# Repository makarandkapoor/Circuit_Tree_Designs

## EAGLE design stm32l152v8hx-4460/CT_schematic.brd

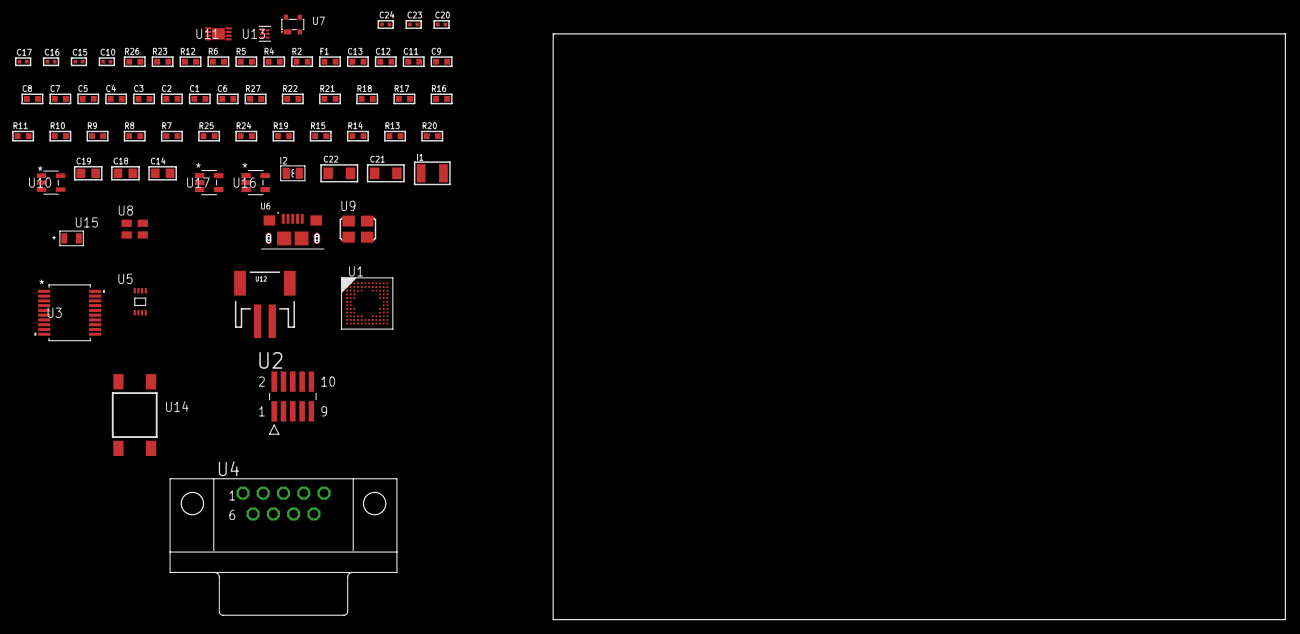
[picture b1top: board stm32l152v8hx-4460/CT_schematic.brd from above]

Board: 2 copper layers, 69 parts (0 on the bottom side), 49 nets, no tracks yet.

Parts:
C1, C2, C3, C4, C5, C7: 1e-07; C0603
C6: 4.7e-06; C0603
C8: 1e-08; C0603
C9, C11, C12, C13: 1e-06; C0603
C10, C20: 1e-07; C0402
C14: 4.7e-06; C0805
C15, C16, C17, C23, C24: 1e-08; C0402
C18, C19: 1e-05; C0805
C21, C22: 1e-05; C1206
F1: 240.0; L0603
I1: 1.5e-05; L1210
I2: 3.3e-06; L0806
R2: 1000.0; R0603
R4: 4700.0; R0603
R5, R6: 2200.0; R0603
R7, R8, R9, R10, R11, R16, R17, R18, R21, R22, R27: 10000.0; R0603
R12: 5.0; R0603
R13, R14, R15: 100000.0; R0603
R19: 220000.0; R0603
R20: 1000000.0; R0603
R23: 9100.0; R0603
R24: 680000.0; R0603
R25: 120000.0; R0603
R26: 2000.0; R0603
U1: STM32L152V8H6; UFBGA100
U2: FTSH-105-01-L-DV-K; SAMTEC_FTSH-105-01-L-DV-K
U3: MAX3218EAP+T; SSOP-20
U4: 182-009-113R531; 182-009-MALE
U5: 24AA128T-I/MNY; TDFN-8/6MM
U6: 10118193-0001LF; FCI_10118193-0001LF
U7: prtr5v0u2ax; SOT143B
U8: ASEK-32.768KHz-ECST; ASEK
U9: ASFL1-25MHZ-NCS; ASFL1
U10: ltc3406es5; TSOT-23-5
U11: MCP73831T-2ACI/MC; DFN8_2X3MC
U12: S2B-PH-SM4-TB(LF)(SN); JST-2-SMD
U13: TPS3895ADRYR; SON-6
U14: 4-1437565-2; SW_4-1437565-2
U15: Q65110A2395; LGM67K-G1J2-24-Z
U16, U17: nc7sz125m5x; NC7SZ125M5X

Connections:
CLK_U1_D1: U1.D1, U8.3
CLK_U1_F1: U1.F1, U9.3
GND: C1.2, C2.2, C3.2, C4.2, C5.2, C6.2, C7.2, C8.2, C9.2, C10.2, C11.2, C12.2, C13.2, C15.2, C16.2, C17.2, C18.2, C19.1, C19.2, C20.2, C21.2, C22.2, C23.2, C24.2, R2.2, R7.2, R11.2, R12.2, R16.2, R18.2, R19.2, R23.2, R25.2, R26.2, U1.D3, U1.E3, U1.F2, U1.F11, U1.F12, U1.J1, U1.K1, U2.3, U2.5, U3.5, U3.17, U3.20, U4.5, U5.4, U5.7, U6.5, U6.6, U6.7, U6.8, U6.9, U7.1, U8.2, U9.2, U10.2, U11.6, U11.9, U12.2, U13.2, U15.C, U16.2, U16.3, U17.1, U17.3
INPUT_USBPOWER_5V: C21.1, R27.2, U6.1, U7.4, U11.1, U11.2
NET_U1_A3: R5.1, U1.A3, U5.6
NET_U1_A4: R7.1, U1.A4
NET_U1_B3: R6.1, U1.B3, U5.5
NET_U1_E2: C7.1, U1.E2
NET_U1_H2: R4.1, U1.H2, U17.4
NET_U1_M1: C8.1, C9.1, F1.1, U1.L1, U1.M1
NET_U1_M12: U14.3, U14.4
NET_U2_9: R12.1, U2.9
NET_U3_1: I1.1, U3.1
NET_U3_2: R13.1, U3.2
NET_U3_3: R14.1, U3.3
NET_U3_4: R15.1, U3.4
NET_U3_15: C13.1, U3.15
NET_U3_16: C14.2, U3.16
NET_U3_18: C14.1, U3.18
NET_U3_19: C12.1, U3.19
NET_U4_2: U3.12, U4.2
NET_U4_3: U3.14, U4.3
NET_U4_7: U3.11, U4.7
NET_U4_8: U3.13, U4.8
NET_U5_1: R16.1, U5.1
NET_U5_2: R17.1, U5.2
NET_U5_3: R18.1, U5.3
NET_U10_3: I2.1, U10.3
NET_U10_5: R19.1, R20.1, U10.5
NET_U10_ATNET_3: I2.2, R20.2
NET_U11_5: R27.1, U11.5
NET_U11_8: R26.1, U11.8
NET_U13_1: R22.1, R23.1, U13.1
NET_U13_3: R24.2, R25.1, U13.3
NET_U13_4: R21.1, U13.4, U16.4, U17.2
NET_U14_1: R2.1, U14.1, U14.2
PROC_SYS_JTCK_SWCLK: R11.1, U1.A10, U2.4
PROC_SYS_JTDI: R9.1, U1.A9, U2.8
PROC_SYS_JTDO_TRACESWO: U1.A8, U2.6
PROC_SYS_JTMS_SWDIO: R10.1, U1.A11, U2.2
PROC_USART2_CTS: U1.B8, U3.8
PROC_USART2_RTS: U1.B7, U3.10
PROC_USART2_RX: U1.B6, U3.9
PROC_USART2_TX: U1.A6, U3.7
PROC_USB_DM: U1.B12, U6.2, U7.3
PROC_USB_DP: U1.A12, U6.3, U7.2
RST_OUT_U2_JTAG_RST_B: R8.1, U2.10, U16.1
VCC_S1_3V7: C18.1, C22.1, U10.4, U11.3, U11.4, U12.1
VCC_TIER1_3V3: C1.1, C2.1, C3.1, C4.1, C5.1, C6.1, C10.1, C11.1, C15.1, C16.1, C17.1, C19.2, C20.1, C23.1, C24.1, F1.2, I1.2, I2.2, R4.2, R5.2, R6.2, R8.2, R9.2, R10.2, R13.2, R14.2, R15.2, R17.2, R20.2, R21.2, R22.2, R24.1, U1.C4, U1.G2, U1.G11, U1.G12, U1.H3, U2.1, U3.6, U5.8, U8.4, U9.4, U13.6, U16.5, U17.5

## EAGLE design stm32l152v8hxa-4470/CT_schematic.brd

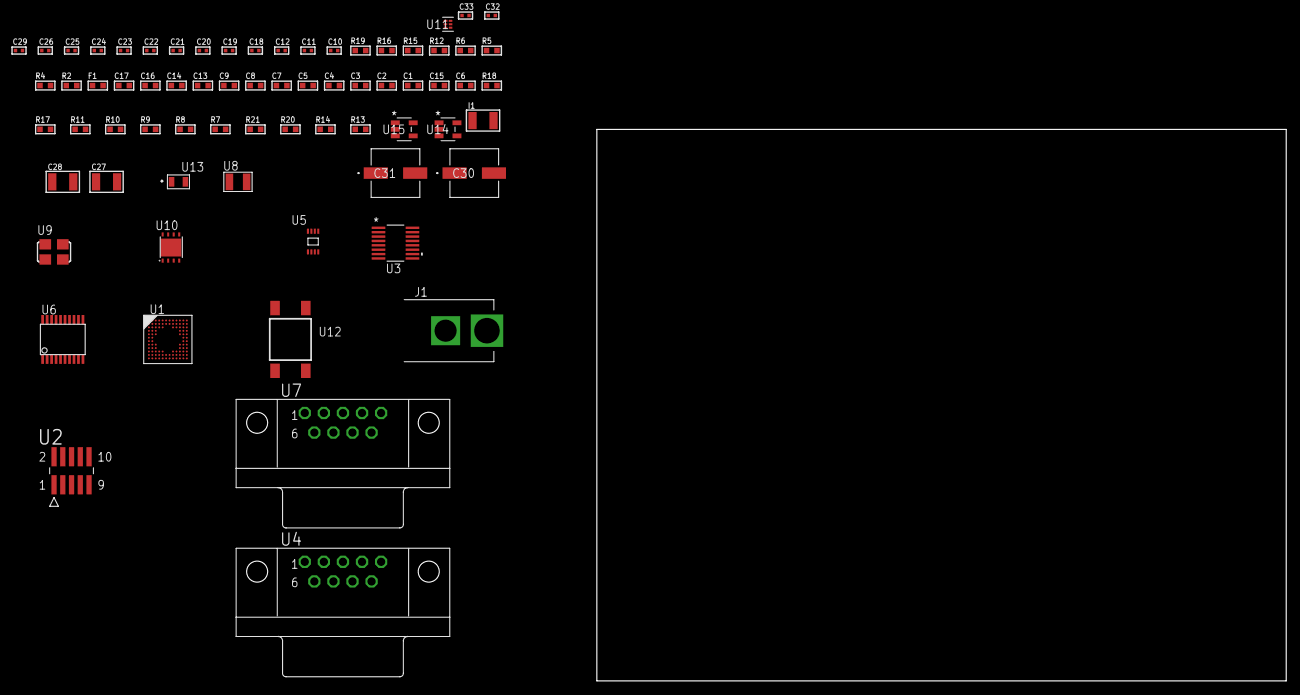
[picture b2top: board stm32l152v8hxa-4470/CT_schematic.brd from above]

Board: 2 copper layers, 100.0 x 80.0 mm, 70 parts (0 on the bottom side), 53 nets, no tracks yet.

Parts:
C1, C2, C3, C4, C5, C7: 1e-07; C0603
C6: 4.7e-06; C0603
C8: 1e-08; C0603
C9, C13, C14, C16, C17: 1e-06; C0603
C10, C11: 1e-11; C0402
C12, C19, C20, C21, C22, C23, C24, C29: 1e-07; C0402
C15: 2.2e-07; C0603
C18, C25, C26, C32, C33: 1e-08; C0402
C27, C28: 1e-05; C1210
C30, C31: 0.0001; EXV-9H
F1: 240.0; L0603
I1: 1e-05; L1210
J1: PJ-037B; PJ-037B_PACKAGE
R2, R16: 1000.0; R0603
R4: 4700.0; R0603
R5, R6: 2200.0; R0603
R7, R8, R9, R10, R11, R17, R18: 10000.0; R0603
R12: 5.0; R0603
R13, R14: 100000.0; R0603
R15: 2231.0; R0603
R19: 9100.0; R0603
R20: 680000.0; R0603
R21: 120000.0; R0603
U1: STM32L152V8H6A; UFBGA100
U2: FTSH-105-01-L-DV-K; SAMTEC_FTSH-105-01-L-DV-K
U3: LTC2804CGN-1#PBF; SSOP-16
U4, U7: 182-009-113R531; 182-009-MALE
U5: 24AA16-I/MC; TDFN-8/6MM
U6: SP3203ECY-L/TR; TSSOP20-I
U8: ABS07-32.768KHZ-7-T
U9: ASFL1-25MHZ-NCS; ASFL1
U10: LP3878SDX-ADJ/NOPB; WSON-8
U11: TPS3895ADRYR; SON-6
U12: 4-1437565-2; SW_4-1437565-2
U13: Q65110A2395; LGM67K-G1J2-24-Z
U14, U15: nc7sz125m5x; NC7SZ125M5X

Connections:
CLK_CRYSTAL_U1_D1: C10.1, U1.D1, U8.1
CLK_CRYSTAL_U1_E1: C11.1, U1.E1, U8.2
CLK_U1_F1: U1.F1, U9.3
GND: C1.2, C2.2, C3.2, C4.2, C5.2, C6.2, C7.2, C8.2, C9.2, C10.2, C11.2, C12.2, C13.2, C14.2, C16.2, C17.2, C18.2, C19.2, C20.2, C23.2, C24.2, C25.2, C26.2, C27.2, C28.2, C29.2, C30.2, C31.2, C32.2, C33.2, J1.2, R2.2, R7.2, R11.2, R12.2, R16.2, R19.2, R21.2, U1.D3, U1.E3, U1.F2, U1.F11, U1.F12, U1.J1, U1.K1, U2.3, U2.5, U3.8, U4.5, U5.4, U5.7, U6.18, U7.5, U9.2, U10.3, U10.PAD, U11.2, U13.C, U14.2, U14.3, U15.1, U15.3
NET_U1_A3: R5.1, U1.A3, U5.6
NET_U1_A4: R7.1, U1.A4
NET_U1_B3: R6.1, U1.B3, U5.5
NET_U1_E2: C7.1, U1.E2
NET_U1_H2: R4.1, U1.H2, U15.4
NET_U1_M1: C8.1, C9.1, F1.1, U1.L1, U1.M1
NET_U1_M12: U12.3, U12.4
NET_U2_9: R12.1, U2.9
NET_U3_6: C13.1, U3.6
NET_U3_7: C15.1, I1.2, U3.7
NET_U3_9: C14.1, U3.9
NET_U3_10: C15.2, U3.10
NET_U3_11: R13.1, U3.11
NET_U4_2: U3.1, U4.2
NET_U4_3: U3.3, U4.3
NET_U4_7: U3.2, U4.7
NET_U4_8: U3.4, U4.8
NET_U6_1: C21.1, U6.1
NET_U6_2: C23.1, U6.2
NET_U6_3: C21.2, U6.3
NET_U6_4: C22.1, U6.4
NET_U6_5: C22.2, U6.5
NET_U6_6: C24.1, U6.6
NET_U7_2: U6.14, U7.2
NET_U7_3: U6.17, U7.3
NET_U7_7: U6.13, U7.7
NET_U7_8: U6.16, U7.8
NET_U10_1: C26.1, U10.1
NET_U10_6: R15.2, R16.1, U10.6
NET_U10_8: R14.1, U10.8
NET_U11_1: R18.1, R19.1, U11.1
NET_U11_3: R20.2, R21.1, U11.3
NET_U11_4: R17.1, U11.4, U14.4, U15.2
NET_U12_1: R2.1, U12.1, U12.2
PROC_SYS_JTCK_SWCLK: R11.1, U1.A10, U2.4
PROC_SYS_JTDI: R9.1, U1.A9, U2.8
PROC_SYS_JTDO_TRACESWO: U1.A8, U2.6
PROC_SYS_JTMS_SWDIO: R10.1, U1.A11, U2.2
PROC_USART1_CTS: U1.B12, U6.8
PROC_USART1_RTS: U1.A12, U6.10
PROC_USART1_RX: U1.B4, U6.11
PROC_USART1_TX: U1.B5, U6.7
PROC_USART2_CTS: U1.B8, U3.13
PROC_USART2_RTS: U1.B7, U3.15
PROC_USART2_RX: U1.B6, U3.16
PROC_USART2_TX: U1.A6, U3.14
RST_OUT_U2_JTAG_RST_B: R8.1, U2.10, U14.1
VCC_S1_14V2: C27.1, C30.1, C31.1, J1.1, R14.2, U10.4
VCC_TIER1_3V3: C1.1, C2.1, C3.1, C4.1, C5.1, C6.1, C12.1, C16.1, C17.1, C18.1, C19.1, C20.1, C25.1, C28.1, C29.1, C32.1, C33.1, F1.2, I1.1, R4.2, R5.2, R6.2, R8.2, R9.2, R10.2, R13.2, R15.1, R17.2, R18.2, R20.1, U1.C4, U1.G2, U1.G11, U1.G12, U1.H3, U2.1, U3.5, U3.12, U5.8, U6.12, U6.19, U9.4, U10.5, U11.6, U14.5, U15.5

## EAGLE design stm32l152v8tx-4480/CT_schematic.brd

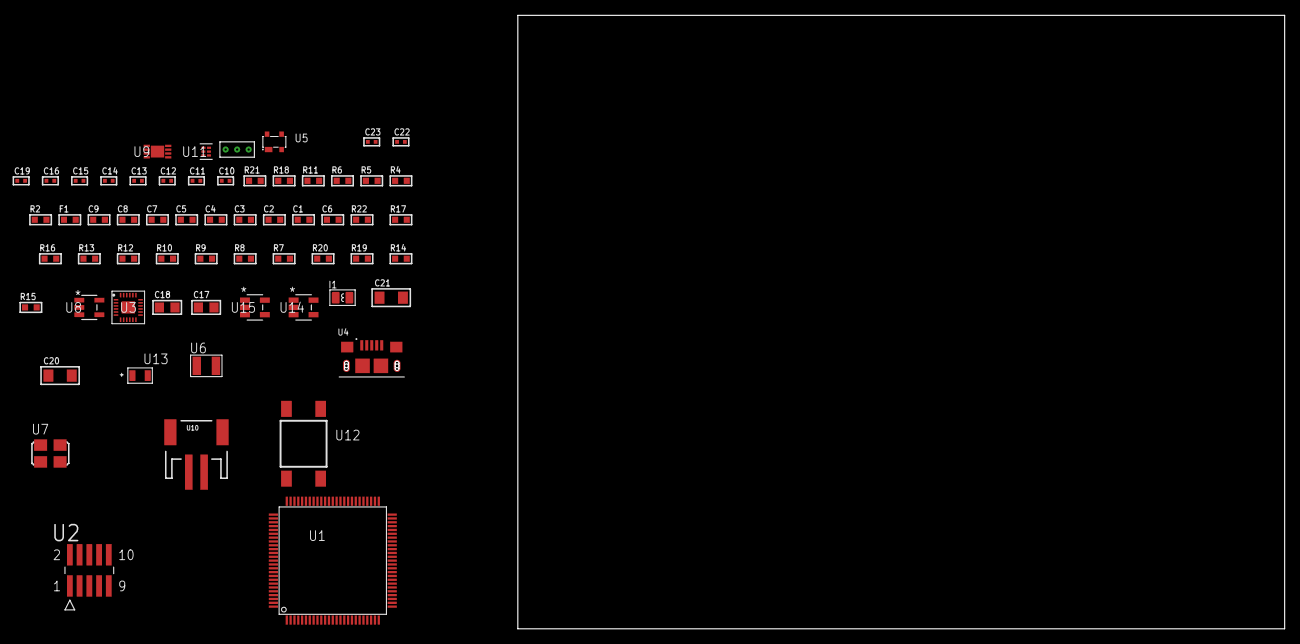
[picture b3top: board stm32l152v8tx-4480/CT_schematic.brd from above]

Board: 2 copper layers, 122.6 x 80.0 mm, 61 parts (0 on the bottom side), 37 nets, no tracks yet.

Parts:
C1, C2, C3, C4, C5, C7: 1e-07; C0603
C6: 4.7e-06; C0603
C8: 1e-08; C0603
C9: 1e-06; C0603
C10, C11: 1e-11; C0402
C12, C13, C14, C19: 1e-07; C0402
C15, C16, C22, C23: 1e-08; C0402
C17, C18: 1e-05; C0805
C20, C21: 1e-05; C1206
F1: 240.0; L0603
I1: 3.3e-06; L0806
R2: 1000.0; R0603
R4: 4700.0; R0603
R5, R6: 2200.0; R0603
R7, R8, R9, R10, R12, R13, R16, R17, R22: 10000.0; R0603
R11: 5.0; R0603
R14: 220000.0; R0603
R15: 1000000.0; R0603
R18: 9100.0; R0603
R19: 680000.0; R0603
R20: 120000.0; R0603
R21: 2000.0; R0603
U1: STM32L152V8T6; LQFP100
U2: FTSH-105-01-L-DV-K; SAMTEC_FTSH-105-01-L-DV-K
U3: MPU-9250; QFN24_2
U4: 10118193-0001LF; FCI_10118193-0001LF
U5: prtr5v0u2ax; SOT143B
U6: ABS07-32.768KHZ-7-T
U7: ASFL1-25MHZ-NCS; ASFL1
U8: ltc3406es5; TSOT-23-5
U9: MCP73831T-2ACI/MC; DFN8_2X3MC
U10: S2B-PH-SM4-TB(LF)(SN); JST-2-SMD
U11: TPS3895ADRYR; SON-6
U12: 4-1437565-2; SW_4-1437565-2
U13: Q65110A2395; LGM67K-G1J2-24-Z
U14, U15: nc7sz125m5x; NC7SZ125M5X
U16: Dummy; DUMMY_PACKAGE_138

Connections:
CLK_CRYSTAL_U1_8: C10.1, U1.8, U6.1
CLK_CRYSTAL_U1_9: C11.1, U1.9, U6.2
CLK_U1_12: U1.12, U7.3
GND: C1.2, C2.2, C3.2, C4.2, C5.2, C6.2, C7.2, C8.2, C9.2, C10.2, C11.2, C12.2, C13.2, C14.2, C15.2, C16.2, C17.2, C18.1, C18.2, C19.2, C20.2, C21.2, C22.2, C23.2, R2.2, R7.2, R11.2, R14.2, R18.2, R20.2, R21.2, U1.10, U1.19, U1.20, U1.27, U1.49, U1.74, U1.99, U2.3, U2.5, U3.18, U3.20, U3.25, U4.5, U4.6, U4.7, U4.8, U4.9, U5.1, U7.2, U8.2, U9.6, U9.9, U10.2, U11.2, U13.C, U14.2, U14.3, U15.1, U15.3, U16.1
INPUT_USBPOWER_5V: C20.1, R22.2, U4.1, U5.4, U9.1, U9.2
NET_U1_6: C7.1, U1.6
NET_U1_14: R4.1, U1.14, U15.4
NET_U1_22: C8.1, C9.1, F1.1, U1.21, U1.22
NET_U1_92: R5.1, U1.92, U3.23
NET_U1_93: R6.1, U1.93, U3.24
NET_U1_94: R7.1, U1.94
NET_U1_98: U12.3, U12.4
NET_U2_9: R11.1, U2.9
NET_U3_9: R13.1, U3.9
NET_U3_10: C13.1, U3.10
NET_U3_22: R12.1, U3.22
NET_U8_3: I1.1, U8.3
NET_U8_5: R14.1, R15.1, U8.5
NET_U8_ATNET_3: I1.2, R15.2
NET_U9_5: R22.1, U9.5
NET_U9_8: R21.1, U9.8
NET_U11_1: R17.1, R18.1, U11.1
NET_U11_3: R19.2, R20.1, U11.3
NET_U11_4: R16.1, U11.4, U14.4, U15.2
NET_U12_1: R2.1, U12.1, U12.2
PROC_GPIO_TO_U3_FSYNC: U1.2, U3.11
PROC_GPIO_TO_U3_INT_B: U1.1, U3.12
PROC_PE4: U1.3, U16.2
PROC_PE5: U1.4, U16.3
PROC_SYS_JTCK_SWCLK: R9.1, U1.76, U2.4
PROC_SYS_JTDO_TRACESWO: U1.89, U2.6
PROC_SYS_JTMS_SWDIO: R10.1, U1.72, U2.2
PROC_USB_DM: U4.2, U5.3
PROC_USB_DP: U4.3, U5.2
RST_OUT_U2_JTAG_RST_B: R8.1, U2.10, U14.1
VCC_S1_3V7: C17.1, C21.1, U8.4, U9.3, U9.4, U10.1
VCC_TIER1_3V3: C1.1, C2.1, C3.1, C4.1, C5.1, C6.1, C12.1, C14.1, C15.1, C16.1, C18.2, C19.1, C22.1, C23.1, F1.2, I1.2, R4.2, R5.2, R6.2, R8.2, R9.2, R10.2, R12.2, R13.2, R15.2, R16.2, R17.2, R19.1, U1.11, U1.28, U1.50, U1.75, U1.100, U2.1, U3.1, U3.8, U3.13, U7.4, U11.6, U14.5, U15.5

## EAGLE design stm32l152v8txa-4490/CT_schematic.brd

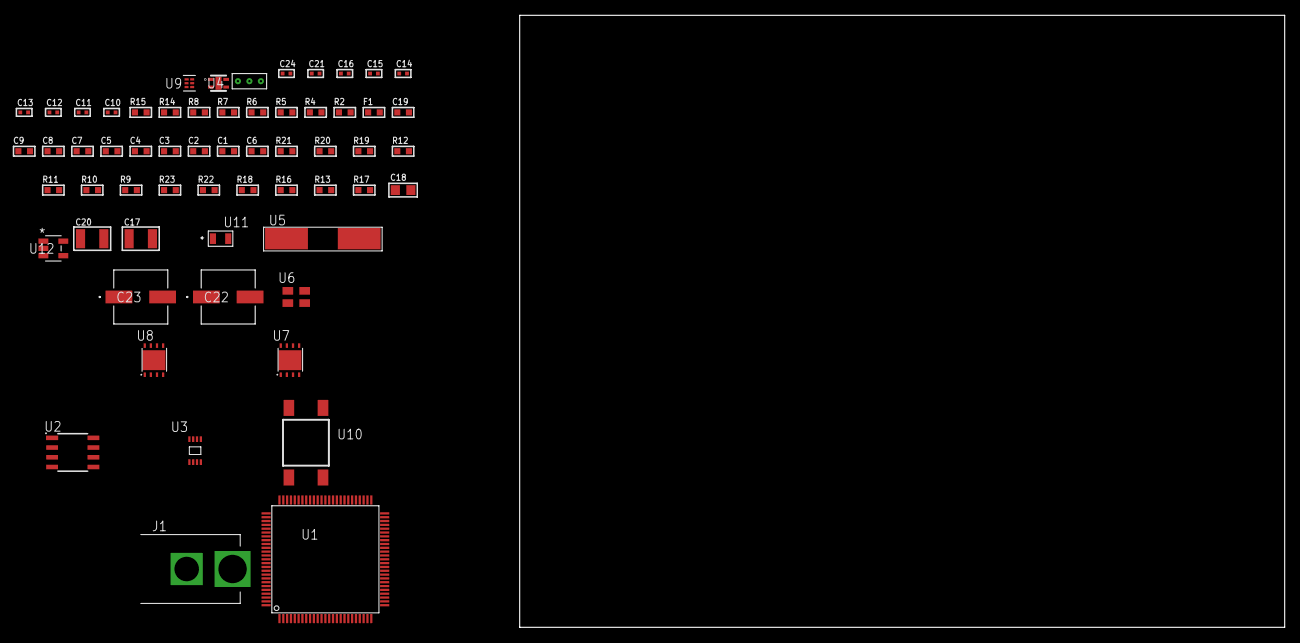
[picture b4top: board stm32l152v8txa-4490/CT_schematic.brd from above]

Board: 2 copper layers, 100.0 x 80.0 mm, 60 parts (0 on the bottom side), 33 nets, no tracks yet.

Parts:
C1, C2, C3, C4, C5, C7: 1e-07; C0603
C6: 4.7e-06; C0603
C8: 1e-08; C0603
C9: 1e-06; C0603
C10, C11: 1e-11; C0402
C12, C13, C15, C16, C24: 1e-08; C0402
C14, C21: 1e-07; C0402
C17, C20: 1e-05; C1210
C18: 1e-05; C0805
C19: 8e-07; R0603
C22, C23: 0.0001; EXV-9H
F1: 240.0; L0603
J1: PJ-037B; PJ-037B_PACKAGE
R2, R15: 1000.0; R0603
R4: 4700.0; R0603
R5, R6, R7, R8: 2200.0; R0603
R9, R10, R11, R12, R19, R20: 10000.0; R0603
R13, R16, R18: 100000.0; R0603
R14: 806.0; R0603
R17: 153694.38; R0603
R21: 82000.0; R0603
R22: 300000.0; R0603
R23: 120000.0; R0603
U1: STM32L152V8T6A; LQFP100
U2: AT25M02-SSHD-T; SOIC-8
U3: 24AA01T-I/MNY; TDFN-8/6MM
U4: Si7034-A10-IM; SI7034-A10-IM
U5: ABLS-25.000MHZ-B2F-T
U6: ASEK-32.768KHz-ECST; ASEK
U7: LP3878SDX-ADJ/NOPB; WSON-8
U8: LP2951ACSDX/NOPB; WSON-8
U9: TPS3895ADRYR; SON-6
U10: 4-1437565-2; SW_4-1437565-2
U11: Q65110A2395; LGM67K-G1J2-24-Z
U12: nc7sz125m5x; NC7SZ125M5X
U13: Dummy; DUMMY_PACKAGE_133

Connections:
CLK_CRYSTAL_U1_12: C10.1, U1.12, U5.1
CLK_CRYSTAL_U1_13: C11.1, U1.13, U5.2
CLK_U1_8: U1.8, U6.3
GND: C1.2, C2.2, C3.2, C4.2, C5.2, C6.2, C7.2, C8.2, C9.2, C10.2, C11.2, C12.2, C13.2, C14.2, C15.2, C16.2, C17.2, C18.2, C19.2, C20.2, C21.2, C22.2, C23.2, C24.2, J1.2, R2.2, R9.2, R15.2, R18.2, R21.2, R23.2, U1.10, U1.19, U1.20, U1.27, U1.49, U1.74, U1.99, U2.4, U3.4, U4.5, U6.2, U7.3, U7.PAD, U8.3, U8.4, U8.PAD, U9.2, U11.C, U12.1, U12.3, U13.1
NET_U1_6: C7.1, U1.6
NET_U1_14: R4.1, U1.14, U12.4
NET_U1_22: C8.1, C9.1, F1.1, U1.21, U1.22
NET_U1_47: R7.1, U1.47, U3.6
NET_U1_48: R8.1, U1.48, U3.5
NET_U1_92: R5.1, U1.92, U4.2
NET_U1_93: R6.1, U1.93, U4.4
NET_U1_94: R9.1, U1.94
NET_U1_98: U10.3, U10.4
NET_U2_3: R10.1, U2.3
NET_U2_7: R12.1, U2.7
NET_U7_1: C16.1, U7.1
NET_U7_6: R14.2, R15.1, U7.6
NET_U7_8: R13.1, U7.8
NET_U8_5: R16.1, U8.5
NET_U8_7: R17.2, R18.1, U8.7
NET_U9_1: R20.1, R21.1, U9.1
NET_U9_3: R22.2, R23.1, U9.3
NET_U9_4: R19.1, U9.4, U12.2
NET_U10_1: R2.1, U10.1, U10.2
PROC_ADC_IN20: U1.53, U13.2
PROC_ADC_IN22: U1.38, U13.3
PROC_SPI1_MISO: U1.31, U2.2
PROC_SPI1_MOSI: U1.32, U2.5
PROC_SPI1_NSS: R11.1, U1.29, U2.1
PROC_SPI1_SCK: U1.30, U2.6
VCC_S1_13V6: C17.1, C19.1, C22.1, C23.1, J1.1, R13.2, U7.4, U8.8
VCC_TIER1_1V8: C1.1, C2.1, C3.1, C4.1, C5.1, C6.1, C12.1, C13.1, C14.1, C18.1, C21.1, C24.1, F1.2, R4.2, R5.2, R6.2, R7.2, R8.2, R10.2, R11.2, R12.2, R14.1, R19.2, R20.2, R22.1, U1.11, U1.28, U1.50, U1.75, U1.100, U2.8, U3.7, U3.8, U4.1, U7.5, U9.6, U12.5
VCC_TIER1_3V3: C15.1, C20.1, R16.2, R17.1, U6.4, U8.1

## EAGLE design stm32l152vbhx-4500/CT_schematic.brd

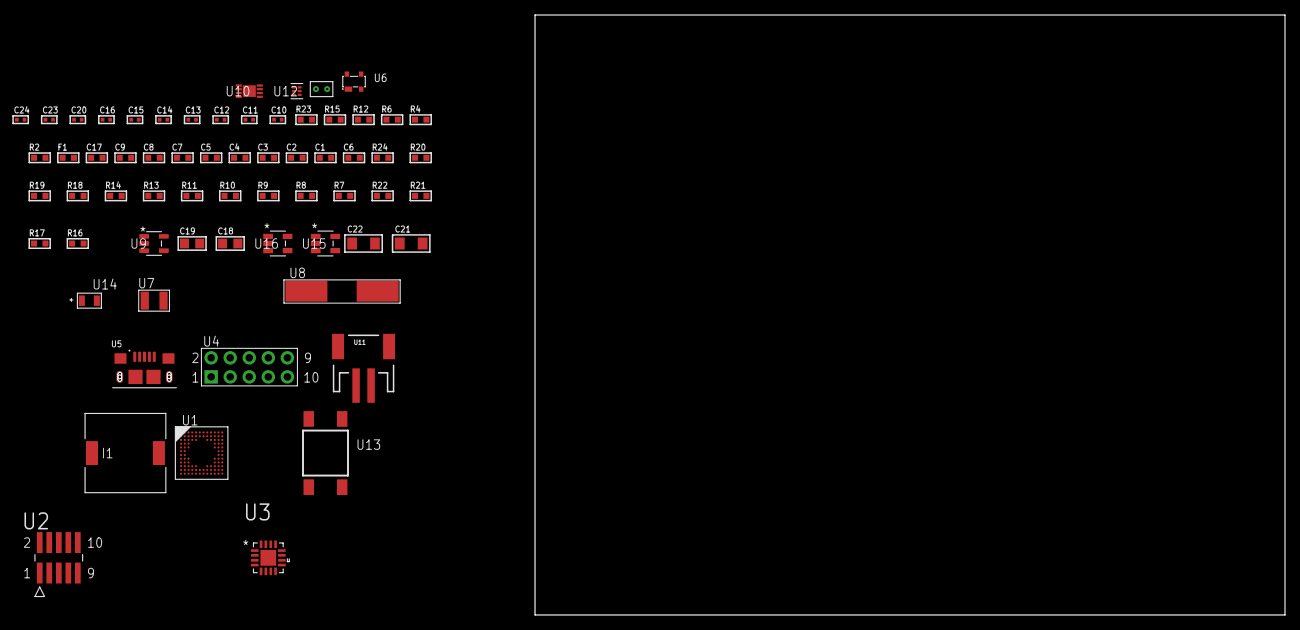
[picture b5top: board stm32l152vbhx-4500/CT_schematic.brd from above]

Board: 2 copper layers, 64 parts (0 on the bottom side), 40 nets, no tracks yet.

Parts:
C1, C2, C3, C4, C5, C7: 1e-07; C0603
C6: 4.7e-06; C0603
C8: 1e-08; C0603
C9, C17: 1e-06; C0603
C10, C11, C12, C13: 1e-11; C0402
C14, C15, C16, C20: 1e-07; C0402
C18, C19: 1e-05; C0805
C21, C22: 1e-05; C1206
C23, C24: 1e-08; C0402
F1: 240.0; L0603
I1: 5.2e-06; DR1040
R2: 1000.0; R0603
R4: 4700.0; R0603
R6: 2200.0; R0603
R7, R8, R9, R10, R11, R13, R14, R18, R19, R24: 10000.0; R0603
R12: 5.0; R0603
R15: 47.0; R0603
R16: 309473.68421053; R0603
R17: 1000000.0; R0603
R20: 18000.0; R0603
R21: 470000.0; R0603
R22: 120000.0; R0603
R23: 2000.0; R0603
U1: STM32L152VBH6; UFBGA100
U2: FTSH-105-01-L-DV-K; SAMTEC_FTSH-105-01-L-DV-K
U3: TSC2013QRSARQ1; QFN65P400X400X100-17N
U4: HTSS-105-01-G-D
U5: 10118193-0001LF; FCI_10118193-0001LF
U6: prtr5v0u2ax; SOT143B
U7: ABS07-32.768KHZ-7-T
U8: ABLS-25.000MHZ-B2F-T
U9: ltc3406es5; TSOT-23-5
U10: MCP73831T-2ACI/MC; DFN8_2X3MC
U11: S2B-PH-SM4-TB(LF)(SN); JST-2-SMD
U12: TPS3895ADRYR; SON-6
U13: 4-1437565-2; SW_4-1437565-2
U14: Q65110A2395; LGM67K-G1J2-24-Z
U15, U16: nc7sz125m5x; NC7SZ125M5X
U17: Dummy; DUMMY_PACKAGE_135

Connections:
CLK_CRYSTAL_U1_D1: C10.1, U1.D1, U7.1
CLK_CRYSTAL_U1_E1: C11.1, U1.E1, U7.2
CLK_CRYSTAL_U1_F1: C12.1, U1.F1, U8.1
CLK_CRYSTAL_U1_G1: C13.1, U1.G1, U8.2
GND: C1.2, C2.2, C3.2, C4.2, C5.2, C6.2, C7.2, C8.2, C9.2, C10.2, C11.2, C12.2, C13.2, C14.2, C18.2, C19.1, C19.2, C20.2, C21.2, C22.2, C23.2, C24.2, R2.2, R7.2, R11.2, R12.2, R16.2, R20.2, R22.2, R23.2, U1.D3, U1.E3, U1.F2, U1.F11, U1.F12, U1.J1, U1.K1, U2.3, U2.5, U3.17, U4.9, U5.5, U5.6, U5.7, U5.8, U5.9, U6.1, U9.2, U10.6, U10.9, U11.2, U12.2, U14.C, U15.2, U15.3, U16.1, U16.3, U17.1
INPUT_USBPOWER_5V: C21.1, R24.2, U5.1, U6.4, U10.1, U10.2
NET_U1_A4: R7.1, U1.A4
NET_U1_B3: R6.1, U1.B3, U3.1
NET_U1_E2: C7.1, U1.E2
NET_U1_H2: R4.1, U1.H2, U16.4
NET_U1_M1: C8.1, C9.1, F1.1, U1.L1, U1.M1
NET_U1_M12: U13.3, U13.4
NET_U2_9: R12.1, U2.9
NET_U3_4: R14.1, U3.4
NET_U3_5: R13.1, U3.5
NET_U3_9: C15.2, C16.2, C17.2, R15.2, U3.9
NET_U3_15: R15.1, U3.8, U3.15
NET_U4_3: U3.12, U4.3
NET_U4_4: U3.14, U4.4
NET_U4_5: U3.11, U4.5
NET_U4_6: U3.13, U4.6
NET_U9_3: I1.1, U9.3
NET_U9_5: R16.1, R17.1, U9.5
NET_U9_ATNET_3: I1.2, R17.2
NET_U10_5: R24.1, U10.5
NET_U10_8: R23.1, U10.8
NET_U12_1: R19.1, R20.1, U12.1
NET_U12_3: R21.2, R22.1, U12.3
NET_U12_4: R18.1, U12.4, U15.4, U16.2
NET_U13_1: R2.1, U13.1, U13.2
PROC_DAC_OUT2: U1.K4, U17.2
PROC_SYS_JTCK_SWCLK: R11.1, U1.A10, U2.4
PROC_SYS_JTDI: R9.1, U1.A9, U2.8
PROC_SYS_JTDO_TRACESWO: U1.A8, U2.6
PROC_SYS_JTMS_SWDIO: R10.1, U1.A11, U2.2
PROC_USB_DM: U1.B12, U5.2, U6.3
PROC_USB_DP: U1.A12, U5.3, U6.2
RST_OUT_U2_JTAG_RST_B: R8.1, U2.10, U15.1
VCC_S1_3V7: C18.1, C22.1, U9.4, U10.3, U10.4, U11.1
VCC_TIER1_2V5: C1.1, C2.1, C3.1, C4.1, C5.1, C6.1, C14.1, C15.1, C16.1, C17.1, C19.2, C20.1, C23.1, C24.1, F1.2, I1.2, R4.2, R6.2, R8.2, R9.2, R10.2, R13.2, R14.2, R17.2, R18.2, R19.2, R21.1, U1.C4, U1.G2, U1.G11, U1.G12, U1.H3, U2.1, U3.7, U3.10, U12.6, U15.5, U16.5

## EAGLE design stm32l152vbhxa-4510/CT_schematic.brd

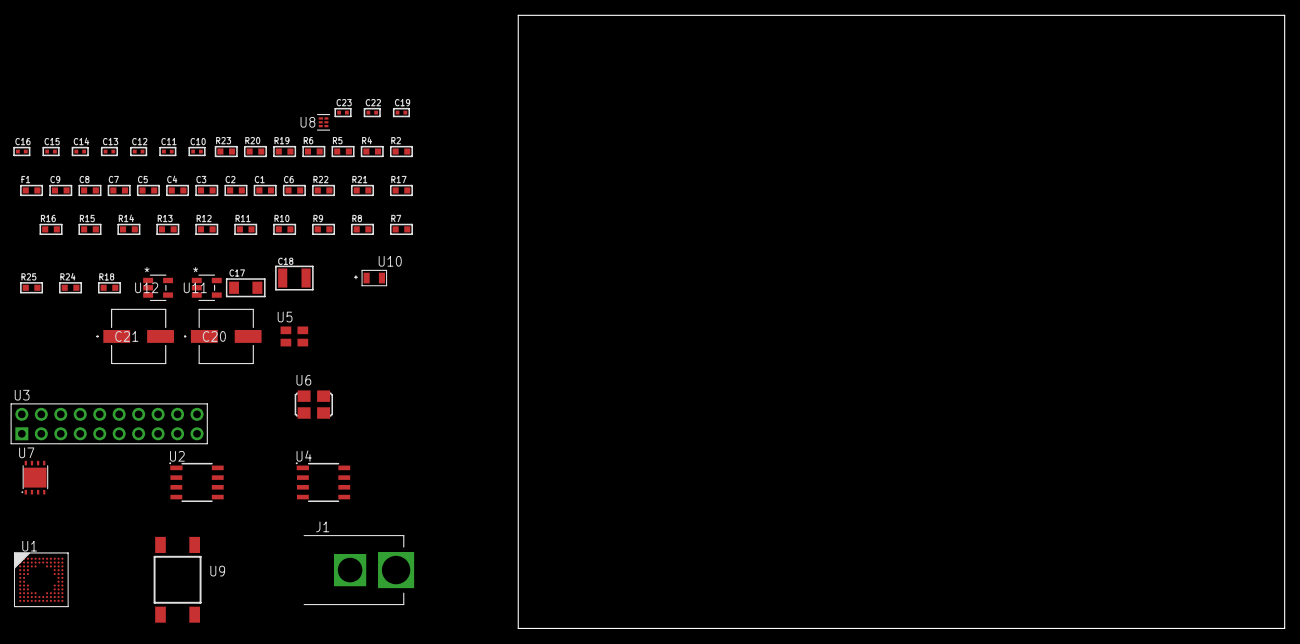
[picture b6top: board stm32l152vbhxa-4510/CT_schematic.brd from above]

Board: 2 copper layers, 100.0 x 80.0 mm, 60 parts (0 on the bottom side), 33 nets, no tracks yet.

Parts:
C1, C2, C3, C4, C5, C7: 1e-07; C0603
C6: 4.7e-06; C0603
C8: 1e-08; C0603
C9: 1e-06; C0603
C10, C13, C14, C15, C16, C22, C23: 1e-08; C0402
C11, C12, C19: 1e-07; C0402
C17: 1e-05; C1206
C18: 1e-05; C1210
C20, C21: 0.0001; EXV-9H
F1: 240.0; L0603
J1: PJ-037B; PJ-037B_PACKAGE
R2, R20: 1000.0; R0603
R4: 4700.0; R0603
R5, R6: 2200.0; R0603
R7, R8, R9, R10, R11, R12, R13, R14, R15, R16, R17, R21, R22: 10000.0; R0603
R18: 100000.0; R0603
R19: 2231.0; R0603
R23: 9100.0; R0603
R24: 680000.0; R0603
R25: 120000.0; R0603
U1: STM32L152VBH6A; UFBGA100
U2: AT25320B-SSHL-T; SOIC-8
U3: TST-110-05-T-D-RA
U4: M24M02-DRMN6TP; SOIC-8
U5: ASEK-32.768KHz-ECST; ASEK
U6: ASFL1-25MHZ-NCS; ASFL1
U7: LP3878SDX-ADJ/NOPB; WSON-8
U8: TPS3895ADRYR; SON-6
U9: 4-1437565-2; SW_4-1437565-2
U10: Q65110A2395; LGM67K-G1J2-24-Z
U11, U12: nc7sz125m5x; NC7SZ125M5X

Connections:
CLK_U1_D1: U1.D1, U5.3
CLK_U1_F1: U1.F1, U6.3
GND: C1.2, C2.2, C3.2, C4.2, C5.2, C6.2, C7.2, C8.2, C9.2, C10.2, C11.2, C12.2, C13.2, C14.2, C15.2, C16.2, C17.2, C18.2, C19.2, C20.2, C21.2, C22.2, C23.2, J1.2, R2.2, R7.2, R16.2, R17.2, R20.2, R23.2, R25.2, U1.D3, U1.E3, U1.F2, U1.F11, U1.F12, U1.J1, U1.K1, U2.4, U3.4, U3.6, U3.8, U3.10, U3.12, U3.14, U3.16, U3.18, U3.20, U4.4, U5.2, U6.2, U7.3, U7.PAD, U8.2, U10.C, U11.2, U11.3, U12.1, U12.3
NET_U1_A3: R5.1, U1.A3, U4.6
NET_U1_A4: R7.1, U1.A4
NET_U1_B3: R6.1, U1.B3, U4.5
NET_U1_E2: C7.1, U1.E2
NET_U1_H2: R4.1, U1.H2, U12.4
NET_U1_M1: C8.1, C9.1, F1.1, U1.L1, U1.M1
NET_U1_M12: U9.3, U9.4
NET_U2_3: R8.1, U2.3
NET_U2_7: R10.1, U2.7
NET_U3_19: R16.1, U3.19
NET_U4_3: R17.1, U4.3
NET_U7_1: C16.1, U7.1
NET_U7_6: R19.2, R20.1, U7.6
NET_U7_8: R18.1, U7.8
NET_U8_1: R22.1, R23.1, U8.1
NET_U8_3: R24.2, R25.1, U8.3
NET_U8_4: R21.1, U8.4, U11.4, U12.2
NET_U9_1: R2.1, U9.1, U9.2
PROC_SPI1_MISO: U1.B12, U2.2
PROC_SPI1_MOSI: U1.A12, U2.5
PROC_SPI1_NSS: R9.1, U1.L9, U2.1
PROC_SPI1_SCK: U1.K4, U2.6
PROC_SYS_JTCK_SWCLK: R14.1, U1.A10, U3.9
PROC_SYS_JTDI: R12.1, U1.A9, U3.5
PROC_SYS_JTDO_TRACESWO: U1.A8, U3.13
PROC_SYS_JTMS_SWDIO: R13.1, U1.A11, U3.7
PROC_SYS_JTRST: R11.1, U1.A7, U3.3
RST_OUT_U3_SRESET_B: R15.1, U3.15, U11.1
VCC_S1_5V8: C17.1, C20.1, C21.1, J1.1, R18.2, U7.4
VCC_TIER1_3V3: C1.1, C2.1, C3.1, C4.1, C5.1, C6.1, C10.1, C11.1, C12.1, C13.1, C14.1, C15.1, C18.1, C19.1, C22.1, C23.1, F1.2, R4.2, R5.2, R6.2, R8.2, R9.2, R10.2, R11.2, R12.2, R13.2, R14.2, R15.2, R19.1, R21.2, R22.2, R24.1, U1.C4, U1.G2, U1.G11, U1.G12, U1.H3, U2.8, U3.1, U3.2, U4.8, U5.4, U6.4, U7.5, U8.6, U11.5, U12.5

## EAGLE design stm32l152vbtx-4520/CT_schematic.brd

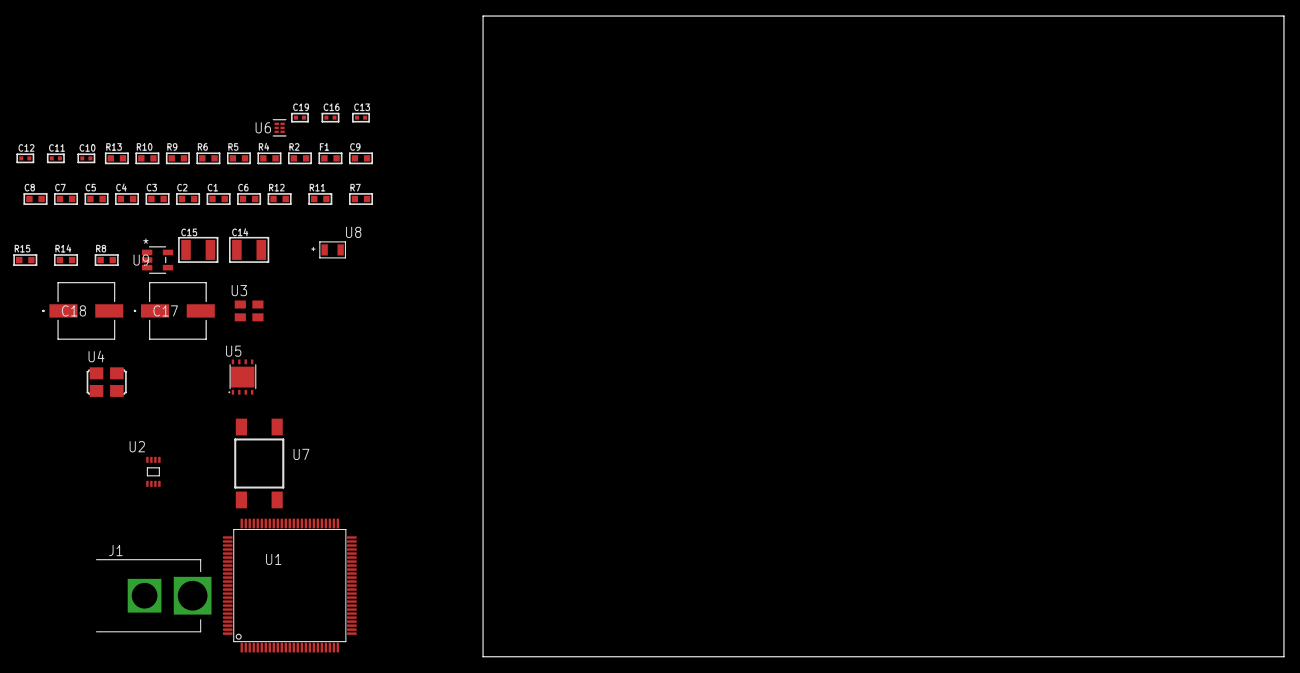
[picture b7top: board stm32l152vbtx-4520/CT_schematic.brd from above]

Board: 2 copper layers, 100.0 x 80.0 mm, 43 parts (0 on the bottom side), 19 nets, no tracks yet.

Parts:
C1, C2, C3, C4, C5, C7: 1e-07; C0603
C6: 4.7e-06; C0603
C8: 1e-08; C0603
C9: 1e-06; C0603
C10, C11, C12, C13, C19: 1e-08; C0402
C14, C15: 1e-05; C1210
C16: 1e-07; C0402
C17, C18: 0.0001; EXV-9H
F1: 240.0; L0603
J1: PJ-037B; PJ-037B_PACKAGE
R2, R10: 1000.0; R0603
R4: 4700.0; R0603
R5, R6: 2200.0; R0603
R7, R11, R12: 10000.0; R0603
R8: 100000.0; R0603
R9: 2231.0; R0603
R13: 9100.0; R0603
R14: 680000.0; R0603
R15: 120000.0; R0603
U1: STM32L152VBT6; LQFP100
U2: 24AA16-I/MC; TDFN-8/6MM
U3: ASEK-32.768KHz-ECST; ASEK
U4: ASFL1-25MHZ-NCS; ASFL1
U5: LP3878SDX-ADJ/NOPB; WSON-8
U6: TPS3895ADRYR; SON-6
U7: 4-1437565-2; SW_4-1437565-2
U8: Q65110A2395; LGM67K-G1J2-24-Z
U9: nc7sz125m5x; NC7SZ125M5X

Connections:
CLK_U1_8: U1.8, U3.3
CLK_U1_12: U1.12, U4.3
GND: C1.2, C2.2, C3.2, C4.2, C5.2, C6.2, C7.2, C8.2, C9.2, C10.2, C11.2, C12.2, C13.2, C14.2, C15.2, C16.2, C17.2, C18.2, C19.2, J1.2, R2.2, R7.2, R10.2, R13.2, R15.2, U1.10, U1.19, U1.20, U1.27, U1.49, U1.74, U1.99, U2.4, U3.2, U4.2, U5.3, U5.PAD, U6.2, U8.C, U9.1, U9.3
NET_U1_6: C7.1, U1.6
NET_U1_14: R4.1, U1.14, U9.4
NET_U1_22: C8.1, C9.1, F1.1, U1.21, U1.22
NET_U1_92: R5.1, U1.92, U2.6
NET_U1_93: R6.1, U1.93, U2.5
NET_U1_94: R7.1, U1.94
NET_U1_98: U7.3, U7.4
NET_U5_1: C13.1, U5.1
NET_U5_6: R9.2, R10.1, U5.6
NET_U5_8: R8.1, U5.8
NET_U6_1: R12.1, R13.1, U6.1
NET_U6_3: R14.2, R15.1, U6.3
NET_U6_4: R11.1, U6.4, U9.2
NET_U7_1: R2.1, U7.1, U7.2
VCC_S1_14V9: C14.1, C17.1, C18.1, J1.1, R8.2, U5.4
VCC_TIER1_3V3: C1.1, C2.1, C3.1, C4.1, C5.1, C6.1, C10.1, C11.1, C12.1, C15.1, C16.1, C19.1, F1.2, R4.2, R5.2, R6.2, R9.1, R11.2, R12.2, R14.1, U1.11, U1.28, U1.50, U1.75, U1.100, U2.7, U2.8, U3.4, U4.4, U5.5, U6.6, U9.5

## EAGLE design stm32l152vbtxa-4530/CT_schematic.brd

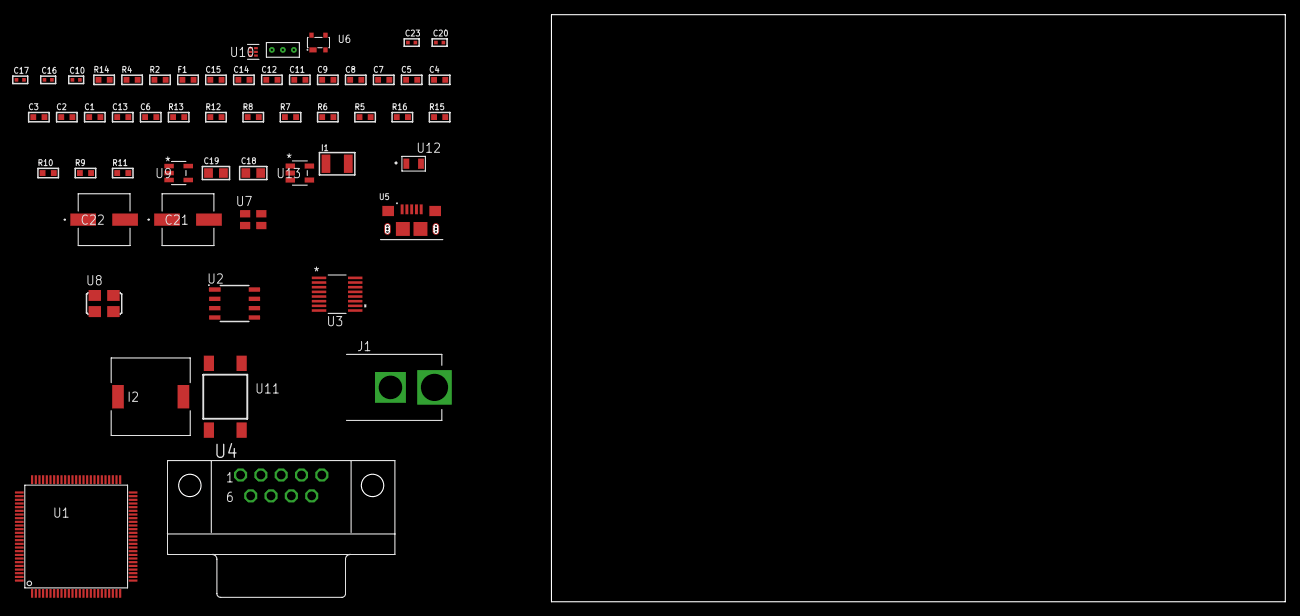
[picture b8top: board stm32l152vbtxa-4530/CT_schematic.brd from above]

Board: 2 copper layers, 122.6 x 80.0 mm, 55 parts (0 on the bottom side), 41 nets, no tracks yet.

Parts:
C1, C2, C3, C4, C5, C7: 1e-07; C0603
C6: 4.7e-06; C0603
C8: 1e-08; C0603
C9, C11, C12, C14, C15: 1e-06; C0603
C10, C16, C17, C23: 1e-08; C0402
C13: 2.2e-07; C0603
C18, C19: 1e-05; C0805
C20: 1e-07; C0402
C21, C22: 0.0001; EXV-9H
F1: 240.0; L0603
I1: 1e-05; L1210
I2: 7e-06; DR1040
J1: PJ-037B; PJ-037B_PACKAGE
R2: 1000.0; R0603
R4: 4700.0; R0603
R5, R6, R7, R8, R12, R13: 10000.0; R0603
R9: 100000.0; R0603
R10: 220000.0; R0603
R11: 1000000.0; R0603
R14: 9100.0; R0603
R15: 680000.0; R0603
R16: 120000.0; R0603
U1: STM32L152VBT6A; LQFP100
U2: AT25512N-SH-T; SOIC-8
U3: LTC2804CGN-1#PBF; SSOP-16
U4: 182-009-113R531; 182-009-MALE
U5: 10118193-0001LF; FCI_10118193-0001LF
U6: prtr5v0u2ax; SOT143B
U7: ASEK-32.768KHz-ECST; ASEK
U8: ASFL1-25MHZ-NCS; ASFL1
U9: ltc3406es5; TSOT-23-5
U10: TPS3895ADRYR; SON-6
U11: 4-1437565-2; SW_4-1437565-2
U12: Q65110A2395; LGM67K-G1J2-24-Z
U13: nc7sz125m5x; NC7SZ125M5X
U14: Dummy; DUMMY_PACKAGE_116

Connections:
CLK_U1_8: U1.8, U7.3
CLK_U1_12: U1.12, U8.3
GND: C1.2, C2.2, C3.2, C4.2, C5.2, C6.2, C7.2, C8.2, C9.2, C10.2, C11.2, C12.2, C14.2, C15.2, C16.2, C17.2, C18.2, C19.1, C19.2, C20.2, C21.2, C22.2, C23.2, J1.2, R2.2, R5.2, R10.2, R14.2, R16.2, U1.10, U1.19, U1.20, U1.27, U1.49, U1.74, U1.99, U2.4, U3.8, U4.5, U5.5, U5.6, U5.7, U5.8, U5.9, U6.1, U7.2, U8.2, U9.2, U10.2, U12.C, U13.1, U13.3, U14.1
NET_U1_6: C7.1, U1.6
NET_U1_14: R4.1, U1.14, U13.4
NET_U1_22: C8.1, C9.1, F1.1, U1.21, U1.22
NET_U1_94: R5.1, U1.94
NET_U1_98: U11.3, U11.4
NET_U2_3: R6.1, U2.3
NET_U2_7: R8.1, U2.7
NET_U3_6: C11.1, U3.6
NET_U3_7: C13.1, I1.2, U3.7
NET_U3_9: C12.1, U3.9
NET_U3_10: C13.2, U3.10
NET_U3_11: R9.1, U3.11
NET_U4_2: U3.1, U4.2
NET_U4_3: U3.3, U4.3
NET_U4_7: U3.2, U4.7
NET_U4_8: U3.4, U4.8
NET_U6_4: U5.1, U6.4
NET_U9_3: I2.1, U9.3
NET_U9_5: R10.1, R11.1, U9.5
NET_U9_ATNET_3: I2.2, R11.2
NET_U10_1: R13.1, R14.1, U10.1
NET_U10_3: R15.2, R16.1, U10.3
NET_U10_4: R12.1, U10.4, U13.2
NET_U11_1: R2.1, U11.1, U11.2
PROC_SPI1_MISO: U1.31, U2.2
PROC_SPI1_MOSI: U1.32, U2.5
PROC_SPI1_NSS: R7.1, U1.29, U2.1
PROC_SPI1_SCK: U1.30, U2.6
PROC_TIM3_CH2: U1.3, U14.2
PROC_TIM3_CH3: U1.35, U14.3
PROC_USART2_CTS: U1.23, U3.13
PROC_USART2_RTS: U1.24, U3.15
PROC_USART2_RX: U1.26, U3.16
PROC_USART2_TX: U1.25, U3.14
PROC_USB_DM: U1.70, U5.2, U6.3
PROC_USB_DP: U1.71, U5.3, U6.2
VCC_S1_4V6: C18.1, C21.1, C22.1, J1.1, U9.4
VCC_TIER1_3V3: C1.1, C2.1, C3.1, C4.1, C5.1, C6.1, C10.1, C14.1, C15.1, C16.1, C17.1, C19.2, C20.1, C23.1, F1.2, I1.1, I2.2, R4.2, R6.2, R7.2, R8.2, R9.2, R11.2, R12.2, R13.2, R15.1, U1.11, U1.28, U1.50, U1.75, U1.100, U2.8, U3.5, U3.12, U7.4, U8.4, U10.6, U13.5
